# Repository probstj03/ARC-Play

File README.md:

# ARC-Play

ARC-Play ist das Zuspielgerät des ARC-Systems. Es spielt den Song eines Shots ab, auf Wunsch mit Vorzähler und
veränderter Geschwindigkeit. Dazu gibt es einen sample-genauen **LTC-Timecode** mit Shot-Userbits aus
(Kamera, Roll, Scene, Shot, Take). Gesteuert wird ARC-Play aus **ARC-Studio** ([ARC-Server](https://github.com/probstj03/ARC-Server))
oder direkt am Gerät über das TFT-Display und den Drehencoder.

## Hardware

- Platine **ARC_AP** (`hardware/ARC_Playback.1`, KiCad 9) mit ESP32-S3-DevKitC-1 N16R8
- PCM5102A-DAC für LTC und Audio, LTC-Eingangsstufe (LM358 + 74HC14), DS3231-RTC, Micro-SD, 2,4"-TFT (ILI9341), Drehencoder KY-040
- **Verdrahtung:** [`hardware/wiring/ARC-Play_Verdrahtung.svg`](hardware/wiring/ARC-Play_Verdrahtung.svg)
- **Bauteile und Pins:** [`hardware/components.txt`](hardware/components.txt)
- **Gehäuse:** `hardware/3D-Druck` (FreeCAD + STL)

Dieselbe Platine wird auch für ARC-Slate verwendet.

## Firmware (v2.0.0-dev)

PlatformIO-Projekt in `firmware/` (Arduino-Framework, ESP32-S3). Zeitbasis, Timecode, Jam Sync und
Netzwerk kommen aus **[ARC-Core](https://github.com/probstj03/ARC-Core)**. Das Repo muss neben
`ARC-Play` liegen, weil es per `symlink://../../ARC-Core` eingebunden wird.

| Modul | Aufgabe |
|---|---|
| ARC-Core | RTC-Uhr, phasengeregelter LTC-Generator, Decoder, Jam Sync mit Prüfphase, Latenz-Loopback, WLAN/ARC-Net, Protokoll v2, Ereignis-Log |
| `play_audio` | Song von SD (`/track.wav`) mit 8-Schläge-Vorzähler, Start und Shot-Ende sample-genau geplant (`at`) |
| `play_ui` | TFT + Drehencoder |
| `play_link` | Play-Protokoll: Shot, Song-Info, WAV-Upload, Lautstärke, Take-Ereignis am Shot-Ende |
| `play_state` | Shot- und Song-Daten |

```bash
cd firmware
cp src/secrets.example.h src/secrets.h   # einmalig: eigene WLANs eintragen
pio run -t upload
pio device monitor -b 115200             # "help" zeigt alle Befehle
```

| Modus | Funktion |
|---|---|
| Free Run | TC = Tageszeit aus der RTC, phasengeregelt |
| Record Run | TC läuft nur während der Aufnahme. Start und Stopp auch geplant (`at`). |
| Playback | Song + LTC ab Shot-Start mit Vorzähler und Tempo, sample-genauer Start und Stopp am Shot-Ende |
| Slave / Jam Sync | TC von J2 übernehmen. Jam → Free Run stellt die RTC µs-genau und prüft 30 s lang. |

Bildraten: 24, 25, 29.97 DF, 30. Kanäle: links = Song (J3), rechts = LTC (J2).

**Bedienung:**
- Drehen = Lautstärke
- Klick = Play/Pause (nach einem Jam: „Kabel abgezogen“ bestätigen)
- Doppelklick = Shot-Auswahl, über ARC-Studio oder ohne Verbindung aus dem gespeicherten Offline-Projekt
- Lang drücken = Einstellungen: Modus, Bildrate, NTP, SD-Karte leeren

**Protokoll:** WebSocket `ws://<ip>/ws`, Protokoll v2 aus ARC-Core.
- Neu sind `hello`, `event` (`take_end` mit µs-Zeit), `pong` und geplante Befehle mit `at`.
- Für das aktuelle ARC-Studio bleiben `newTake`, `status`, `upload_prepared` und `upload_ack` erhalten.

## Stand

- Die Firmware ist neu aufgebaut und noch nicht auf der Hardware getestet.
- Wichtig beim ersten Test:
  - TFT-Anzeige
  - WAV-Wiedergabe mit Vorzähler
  - Stopp am Shot-Ende
  - Jam Sync mit ARC-Slate
- Die Ausgangslatenz der Playback-Ausgabe wird live über J2 nachgeführt. `?` zeigt Latenz und Phasenfehler.
- Offline-Projekt (aus ARC-Studio „Projekt auf Geräte“) liegt in LittleFS. Takes holt ARC-Studio beim nächsten Verbinden ab.
- Offen ist die Leader-Rolle: Ohne ARC-Studio steuert Play die Slate direkt.

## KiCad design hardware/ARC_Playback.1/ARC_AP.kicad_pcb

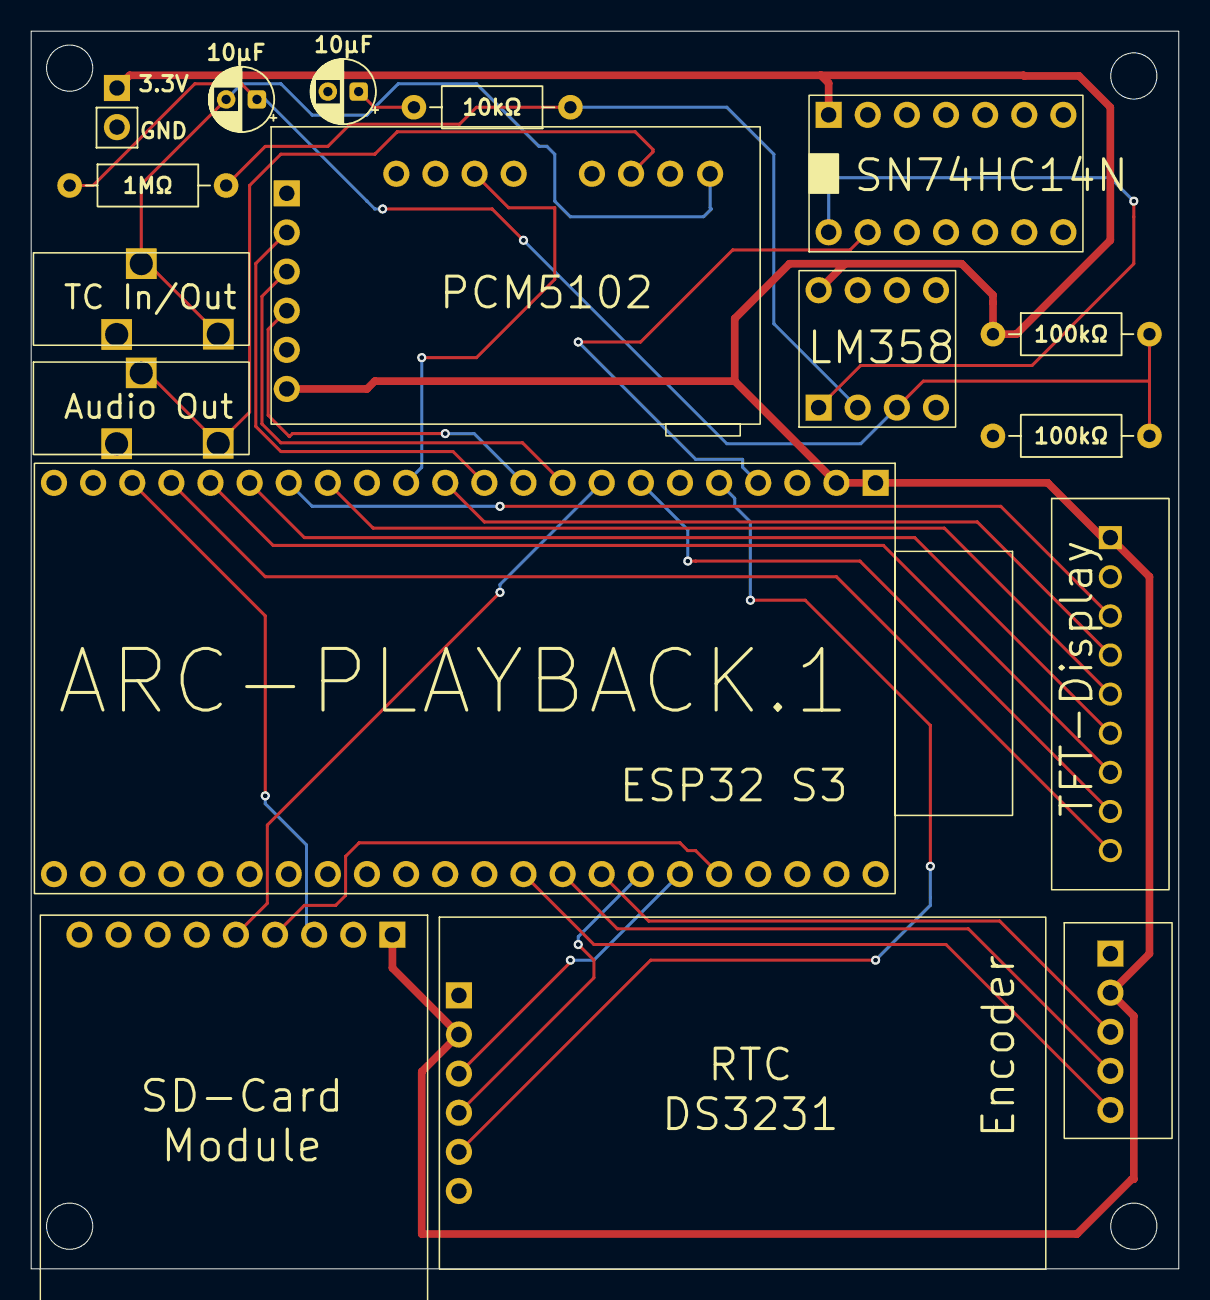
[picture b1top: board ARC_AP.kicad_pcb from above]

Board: 2 copper layers, 74.5 x 80.3 mm, 17 parts (0 on the bottom side), 28 nets.

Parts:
C1, C2: 10nF; CP_Radial_D4.0mm_P2.00mm
J1: Micro_SD_Card_Det1; PinHeader_1x09_P2.54mm_Vertical
J2: TC In/Out; Klinkenbuchse
J3: Playback Out; Klinkenbuchse
J4: Power Supply; PinSocket_1x02_P2.54mm_Vertical
R1, R2: 100kOhm; R_Axial_DIN0207_L6.3mm_D2.5mm_P10.16mm_Horizontal
R3: 1MOhm; R_Axial_DIN0207_L6.3mm_D2.5mm_P10.16mm_Horizontal
R4: 10kOhm; R_Axial_DIN0207_L6.3mm_D2.5mm_P10.16mm_Horizontal
SW1: RotaryEncoder_Switch; PinSocket_1x05_P2.54mm_Vertical
U1: ESP32-S3-DevKitC-1-N32R16V; ESP32S3
U2: DS3231M; PinSocket_1x06_P2.54mm_Vertical
U3: LM358
U4: CR2013-MI2120
U6: SN74HC14N
U7: PCM5102A; PCM5102

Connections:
+3.3V: J1.1 (3V), J4.1, R1.1, SW1.2 (VCC), U1.J111 (3V3_1), U1.J112 (3V3_2), U2.2 (VCC), U3.8 (V+), U4.1 (VCC), U6.14 (VCC), U7.1 (VIN)
GND: C1.2, J1.2 (GND), J2.3, J3.3, J4.2, R2.2, SW1.1 (GND), U1.J132 (G_1), U1.J311 (G_2), U1.J331 (G_3), U1.J332 (G_4), U2.1 (GND), U3.4 (V-), U4.2 (GND), U6.7 (GND), U7.2 (GND), U7.6 (SCK), U7.11 (GND), U7.13 (GND)
unnamed: C1.1, R4.2
unnamed: J1.3 (CLK), U1.J130 (14)
unnamed: J1.5 (CMD), U1.J118 (15)
unnamed: J1.4 (D0), U1.J315 (2)
unnamed: SW1.5 (CLK), U1.J320 (38)
unnamed: SW1.4 (DT), U1.J319 (39)
unnamed: SW1.3 (SW), U1.J318 (40)
unnamed: U1.J123 (3), U7.9 (XSMT_3)
unnamed: U1.J114 (4), U6.2 (1Y)
unnamed: U1.J117 (7), U4.8 (LED)
unnamed: U1.J122 (8), U4.4 (RESET)
unnamed: U1.J125 (9), U4.5 (D/~C)
unnamed: U1.J126 (10), U4.3 (~CS)
unnamed: U1.J127 (11), U4.6 (MOSI)
unnamed: U1.J128 (12), U4.7 (SCK)
unnamed: U1.J129 (13), U4.9 (MISO)
unnamed: U1.J119 (16), U7.4 (DIN)
unnamed: U1.J120 (17), U7.3 (LRCK)
unnamed: U1.J121 (18), U7.5 (BCK)
unnamed: U1.J317 (41), U2.4 (SCL)
unnamed: U1.J316 (42), U2.3 (SDA)
unnamed: C2.1, R1.2, R2.1, R3.1, U3.3 (+)
unnamed: R3.2, R4.1, U3.2 (-)
unnamed: U3.1, U6.1 (1A)
unnamed: C2.2, J2.1, J2.2, U7.14 (OUTL)
unnamed: J3.1, J3.2, U7.12 (OUTR)

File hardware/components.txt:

ARC-Play – Hardware-Komponenten
================================

Mikrocontroller
---------------
U1   ESP32-S3-DevKitC-1                Hauptcontroller (WLAN, I2S, SD_MMC, SPI)
                                       Firmware-Kommentar: N16R8

Audio / Timecode
----------------
U7   PCM5102A Audio-DAC (I2S)          LTC- und WAV-Ausgabe
                                       BCK GPIO18, LRCK GPIO17, DIN GPIO16, XSMT (Mute) GPIO3
U3   LM358 Operationsverstärker        Eingangsstufe für eingehenden LTC
U6   SN74HC14N Schmitt-Trigger         Signalaufbereitung LTC-Eingang -> GPIO4
J2   3,5 mm Klinkenbuchse (TRS)        "TC In/Out" – Timecode-Ein-/Ausgang
R1   100 kΩ                            Widerstand (THT, 0207)
R2   100 kΩ                            Widerstand (THT, 0207)
R3   1 MΩ                              Widerstand (THT, 0207)
R4   10 kΩ                             Widerstand (THT, 0207)
C1   10 nF                             Kondensator
C2   10 nF                             Kondensator

Echtzeituhr
-----------
U2   DS3231(M) RTC-Modul               I2C: SDA GPIO42, SCL GPIO41, SQW (1 Hz) GPIO5
     CR2032-Knopfzelle für RTC         [?] falls Modul mit Batteriehalter

Speicher
--------
J1   Micro-SD-Kartenmodul              SD_MMC 1-Bit: CLK GPIO14, CMD GPIO15, D0 GPIO2
     Micro-SD-Karte                    WAV-Dateien / Projektdaten

Anzeige / Bedienung
-------------------
U4   2,4" TFT-Display 320x240          ILI9341, SPI, mit Touch (Touch nicht verwendet)
                                       MOSI GPIO11, SCLK GPIO12, MISO GPIO13, CS GPIO10,
                                       DC GPIO9, RST GPIO8, Backlight GPIO7
SW1  Drehencoder mit Taster (KY-040)   CLK GPIO38, DT GPIO39, SW GPIO40

Stromversorgung
---------------
J4   Stromversorgungs-Anschluss (2-pin) bisher nur USB

Mechanik
--------
     Platine ARC_AP (eigene Leiterplatte)
     3D-Druck-Gehäuse: Korpus + Deckel (hardware/3D-Druck/ARC_Play.FCStd)
     Stiftleisten / Buchsenleisten 2,54 mm (für Module)
